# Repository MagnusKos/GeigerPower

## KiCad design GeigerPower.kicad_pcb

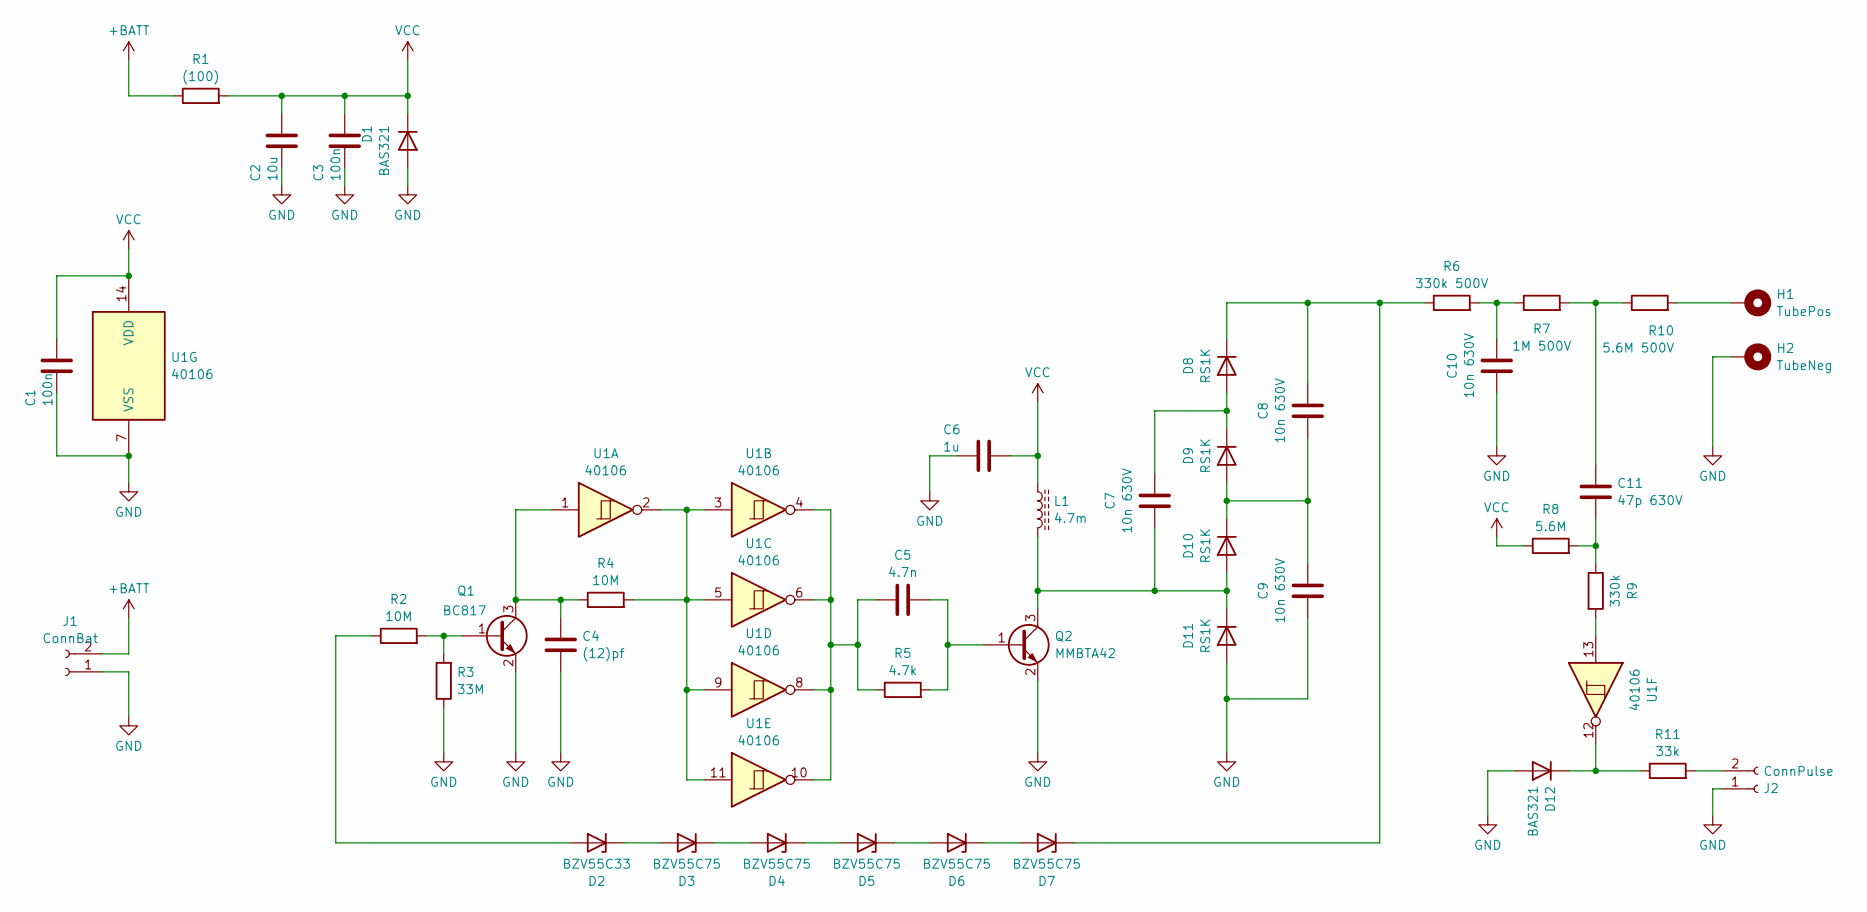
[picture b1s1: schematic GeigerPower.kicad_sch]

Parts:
C1, C3: 100n; C_0805_2012Metric_Pad1.18x1.45mm_HandSolder
C2: 10u; C_0805_2012Metric_Pad1.18x1.45mm_HandSolder
C4: (12)pf; C_0805_2012Metric_Pad1.18x1.45mm_HandSolder
C5: 4.7n; C_0805_2012Metric_Pad1.18x1.45mm_HandSolder
C6: 1u; C_0805_2012Metric_Pad1.18x1.45mm_HandSolder
C7, C8, C9, C10: 10n 630V; C_1206_3216Metric_Pad1.33x1.80mm_HandSolder
C11: 47p 630V; C_1206_3216Metric_Pad1.33x1.80mm_HandSolder
D1, D12: BAS321; D_SOD-323_HandSoldering
D2: BZV55C33; D_MiniMELF
D3, D4, D5, D6, D7: BZV55C75; D_MiniMELF
D8, D9, D10, D11: RS1K; D_SMA_Handsoldering
H1: TubePos; MountingHole_2.7mm_M2.5_DIN965_Pad
H2: TubeNeg; MountingHole_2.7mm_M2.5_DIN965_Pad
J1: ConnBat; JST_XH_S2B-XH-A-1_1x02_P2.50mm_Horizontal
J2: ConnPulse; JST_XH_S2B-XH-A-1_1x02_P2.50mm_Horizontal
L1: 4.7m; L_Radial_D7.8mm_P5.00mm_Fastron_07HCP
Q1: BC817; SOT-23
Q2: MMBTA42; SOT-23
R1: (100); R_0805_2012Metric_Pad1.20x1.40mm_HandSolder
R2, R4: 10M; R_0805_2012Metric_Pad1.20x1.40mm_HandSolder
R3: 33M; R_0805_2012Metric_Pad1.20x1.40mm_HandSolder
R5: 4.7k; R_0805_2012Metric_Pad1.20x1.40mm_HandSolder
R6: 330k 500V; R_2512_6332Metric_Pad1.40x3.35mm_HandSolder
R7: 1M 500V; R_2512_6332Metric_Pad1.40x3.35mm_HandSolder
R8: 5.6M; R_0805_2012Metric_Pad1.20x1.40mm_HandSolder
R9: 330k; R_0805_2012Metric_Pad1.20x1.40mm_HandSolder
R10: 5.6M 500V; R_2512_6332Metric_Pad1.40x3.35mm_HandSolder
R11: 33k; R_0805_2012Metric_Pad1.20x1.40mm_HandSolder
U1: 40106; SOIC-14_3.9x8.7mm_P1.27mm

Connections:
+BATT: J1.2, R1.1
GND: C1.2, C2.2, C3.2, C4.1, C6.2, C9.2, C10.2, D1.2 (A), D11.2 (A), D12.2 (A), H2.1, J1.1, J2.1, Q1.2 (E), Q2.2 (E), R3.1, U1.7 (VSS)
unnamed: C5.2, R5.1, U1.4, U1.6, U1.8, U1.10
unnamed: C10.1, R6.2, R7.1
unnamed: C11.1, R7.2, R10.1
unnamed: C11.2, R8.2, R9.1
unnamed: D2.2 (A), R2.1
unnamed: D2.1 (K), D3.2 (A)
unnamed: D3.1 (K), D4.2 (A)
unnamed: D4.1 (K), D5.2 (A)
unnamed: D5.1 (K), D6.2 (A)
unnamed: D6.1 (K), D7.2 (A)
unnamed: C8.1, D7.1 (K), D8.1 (K), R6.1
unnamed: C7.1, D8.2 (A), D9.1 (K)
unnamed: C7.2, D10.2 (A), D11.1 (K), L1.2, Q2.3 (C)
unnamed: C8.2, C9.1, D9.2 (A), D10.1 (K)
unnamed: D12.1 (K), R11.1, U1.12
unnamed: H1.1, R10.2
unnamed: J2.2, R11.2
unnamed: Q1.1 (B), R2.2, R3.2
unnamed: C4.2, Q1.3 (C), R4.1, U1.1
unnamed: C5.1, Q2.1 (B), R5.2
unnamed: R4.2, U1.2, U1.3, U1.5, U1.9, U1.11
unnamed: R9.2, U1.13
VCC: C1.1, C2.1, C3.1, C6.1, D1.1 (K), L1.1, R1.2, R8.1, U1.14 (VDD)

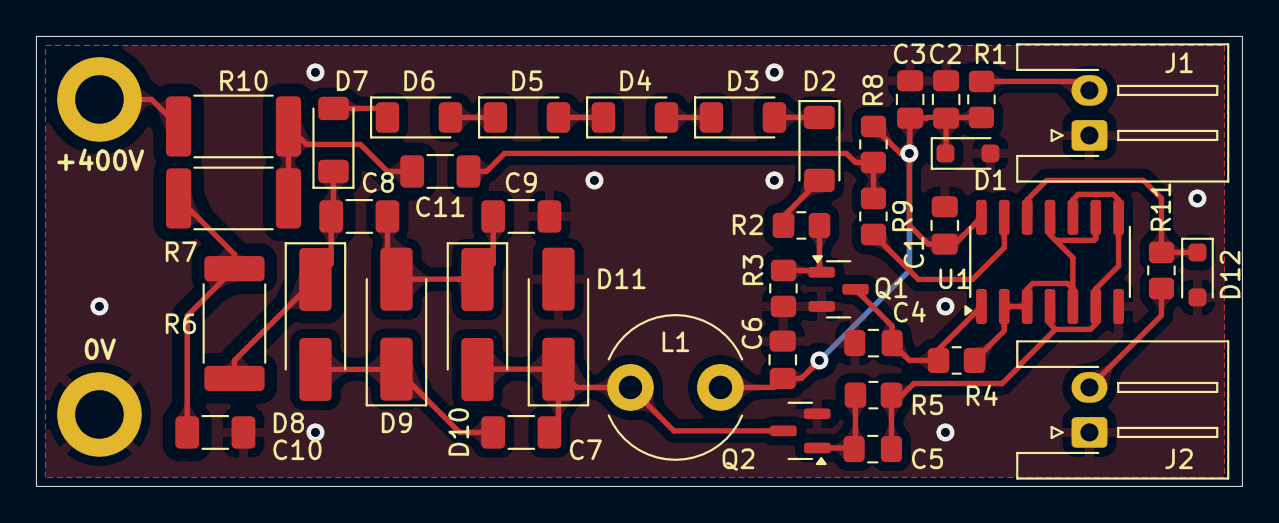
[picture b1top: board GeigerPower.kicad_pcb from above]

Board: 2 copper layers, 67.0 x 25.0 mm, 42 parts (0 on the bottom side), 25 nets.

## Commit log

2024-11-23 KiCad initial commit
    Kicad project files added
2024-11-25 Basic schematics
    Added main circuitry. Assigned symbols and values to (almost) everything.
    ToDo: Power source.
2024-11-26 Input power finished
    Added battery connector, input RC-filter.
    Rewired protection diode from generator to filter output.
2024-11-26 Finished schematics
    Applied some fixes. Assigned symbols.
2024-11-26 Connectors rewired
2024-11-27 First PCB commit
    Added basic PCB design, that can be made with almost no effort.
    Adjustments and fixes will be delivered soon.
2024-11-27 Update GeigerPower.kicad_pcb
    Added conotur. Compactified a bit the layout. Placed silkscreen data.
2024-11-27 Adjustments, HV-rules
    Added high coltage rules. Small silkscreen fixes applied. Another contour edit performed.
